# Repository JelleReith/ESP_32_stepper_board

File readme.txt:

Hi,
Thanks for using this board!

Hardware:
1 x ESP32 Devkit v1
9 x DRV8825 stepper driver
9 x 100uf 50v capacitor
pin_headers or screw terminals.

      //////////////////////BOARD LAYOUT\\\\\\\\\\\\\\\\\\\\\\\
      
 DIPDIP VESPVMOT  DRV0  DRV1  DRV2  DRV3  DRV4  DRV5  DRV6  DRV7  DRV8
 DIPDIP
ESPESPESPESPESP    CAP     DRV0DRV0DRV0  DRV5DRV5DRV5 CAP DRV6DRV6DRV6
ESPESPESPESPESP            DRV0DRV0DRV0  DRV5DRV5DRV5     DRV6DRV6DRV6
ESPESPESPESPESP            DRV0DRV0DRV0  DRV5DRV5DRV5 CAP DRV6DRV6DRV6
ESPESPESPESPESP
ESPESPESPESPESP    CAP     DRV1DRV1DRV1  DRV4DRV4DRV4 CAP DRV7DRV7DRV7
ESPESPESPESPESP            DRV1DRV1DRV1  DRV4DRV4DRV4     DRV7DRV7DRV7
ESPESPESPESPESP            DRV1DRV1DRV1  DRV4DRV4DRV4 CAP DRV7DRV7DRV7
ESPESPESPESPESP
ESPESPESPESPESP    CAP     DRV3DRV2DRV2  DRV3DRV3DRV3 CAP DRV8DRV8DRV8
ESPESPESPESPESP            DRV3DRV2DRV2  DRV3DRV3DRV3 CAP DRV8DRV8DRV8
ESPESPESPESPESP            DRV3DRV2DRV2  DRV3DRV3DRV3 CAP DRV8DRV8DRV8

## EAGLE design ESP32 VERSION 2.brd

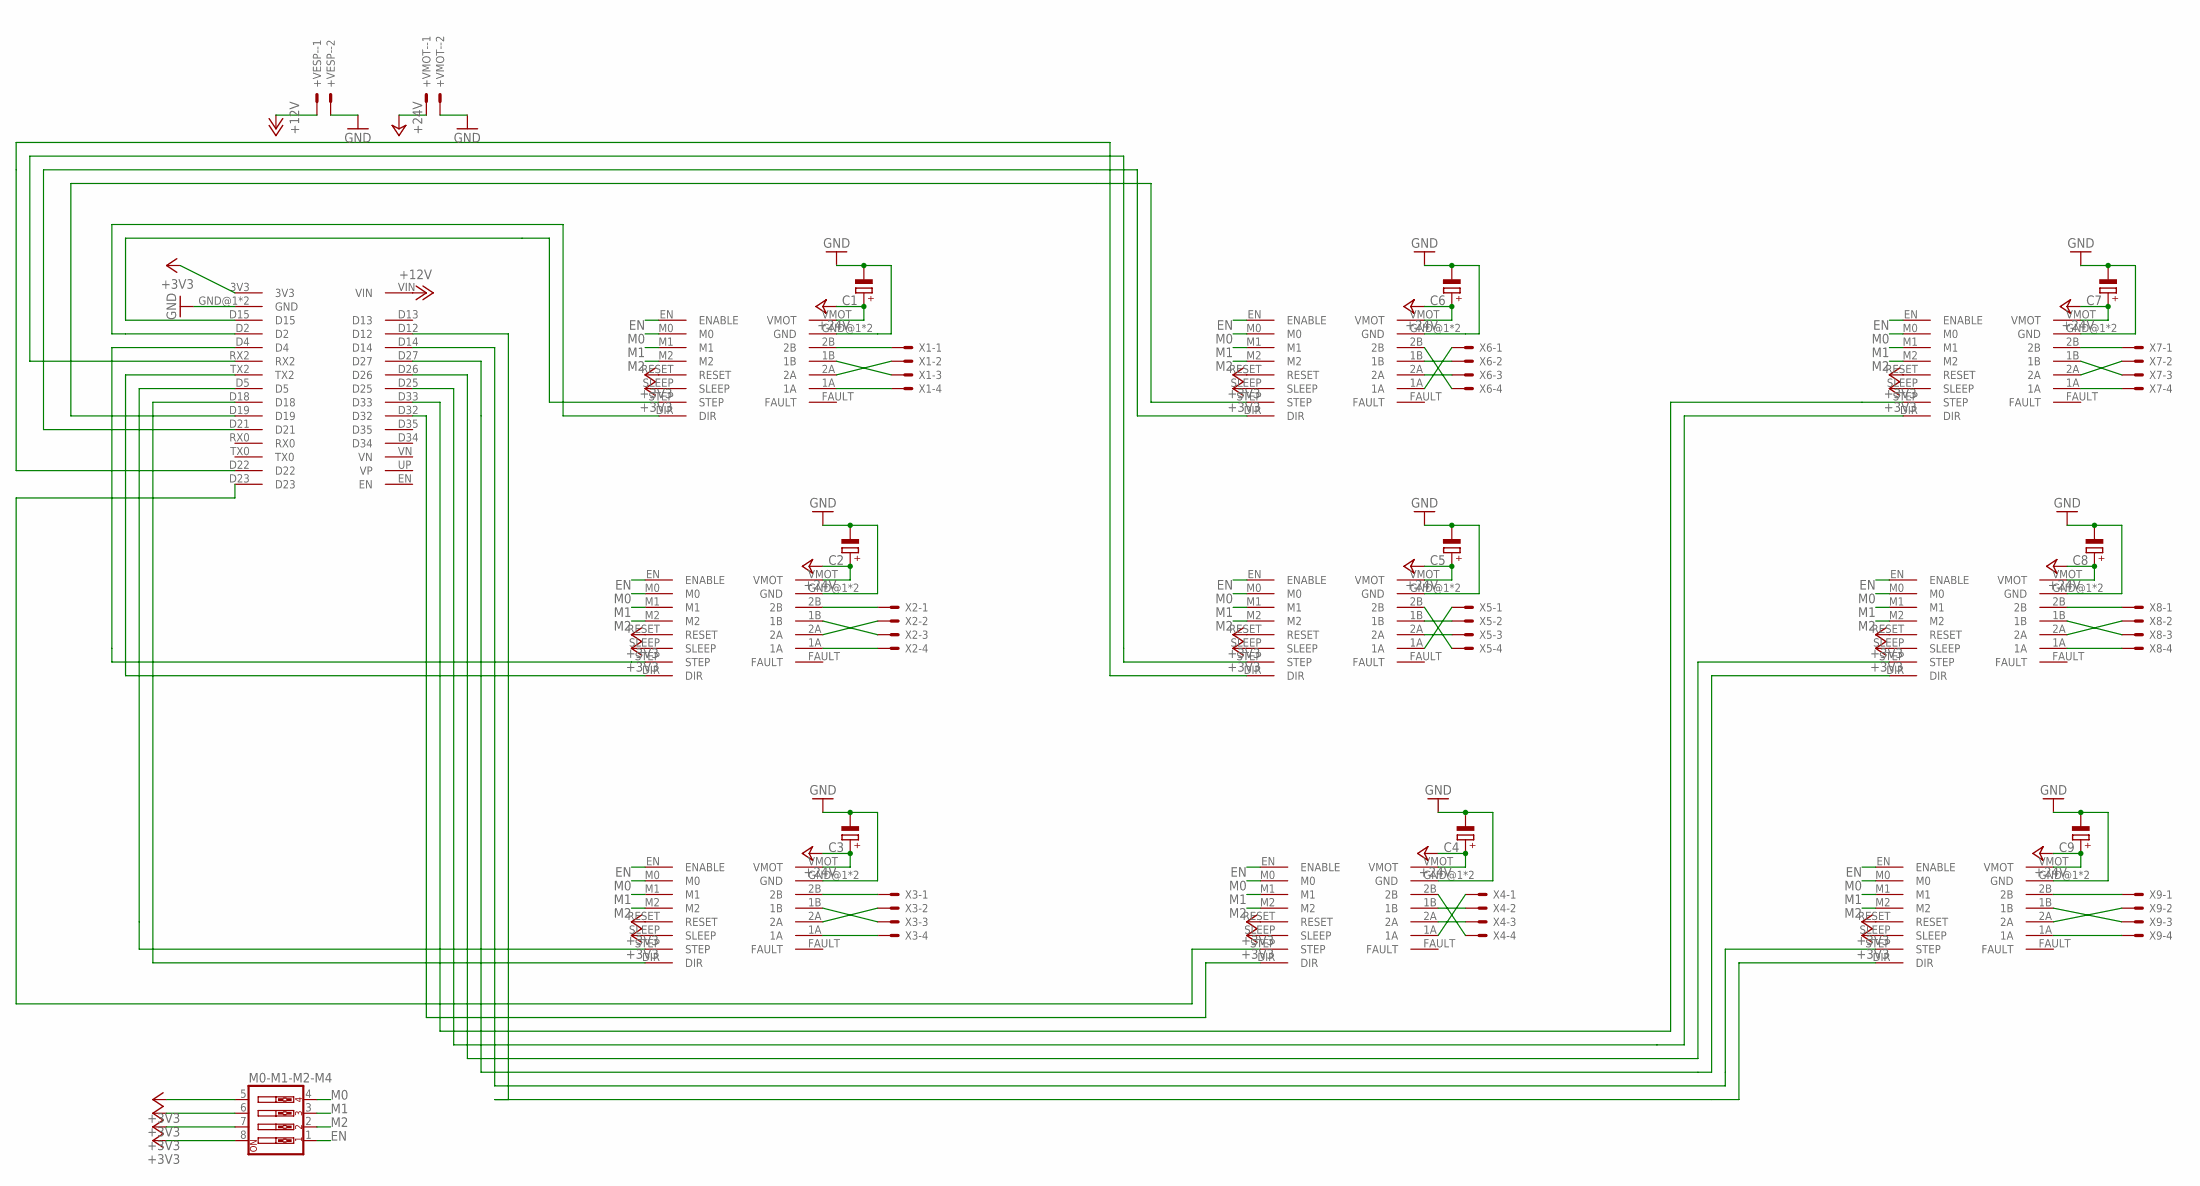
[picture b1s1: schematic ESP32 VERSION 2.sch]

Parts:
+VESP-: 22-23-2021
+VMOT-: 22-23-2021
C1, C2, C3, C4, C5, C6, C7, C8, C9: CPOL-EUE3.5-8; E3,5-8
M0-M1-M2-M4: SW_DIP-4; EDG-04
U$1, U$2, U$4, U$5, U$6, U$7, U$8, U$9: DRV8825
U$3: STEPPER 0; DRV8825
U$10: ESP32
X1, X2, X3, X4, X5, X6, X7, X8, X9: 22-23-2041

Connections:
+3V3: M0-M1-M2-M4.5, M0-M1-M2-M4.6, M0-M1-M2-M4.7, M0-M1-M2-M4.8, U$1.RESET, U$1.SLEEP, U$2.RESET, U$2.SLEEP, U$3.RESET, U$3.SLEEP, U$4.RESET, U$4.SLEEP, U$5.RESET, U$5.SLEEP, U$6.RESET, U$6.SLEEP, U$7.RESET, U$7.SLEEP, U$8.RESET, U$8.SLEEP, U$9.RESET, U$9.SLEEP, U$10.3V3
+12V: +VESP-.1, U$10.VIN
+24V: +VMOT-.1, C1.+, C2.+, C3.+, C4.+, C5.+, C6.+, C7.+, C8.+, C9.+, U$1.VMOT, U$2.VMOT, U$3.VMOT, U$4.VMOT, U$5.VMOT, U$6.VMOT, U$7.VMOT, U$8.VMOT, U$9.VMOT
EN: M0-M1-M2-M4.1, U$1.EN (ENABLE), U$2.EN (ENABLE), U$3.EN (ENABLE), U$4.EN (ENABLE), U$5.EN (ENABLE), U$6.EN (ENABLE), U$7.EN (ENABLE), U$8.EN (ENABLE), U$9.EN (ENABLE)
GND: +VESP-.2, +VMOT-.2, C1.-, C2.-, C3.-, C4.-, C5.-, C6.-, C7.-, C8.-, C9.-, U$1.GND@1 (GND), U$1.GND@2 (GND), U$2.GND@1 (GND), U$2.GND@2 (GND), U$3.GND@1 (GND), U$3.GND@2 (GND), U$4.GND@1 (GND), U$4.GND@2 (GND), U$5.GND@1 (GND), U$5.GND@2 (GND), U$6.GND@1 (GND), U$6.GND@2 (GND), U$7.GND@1 (GND), U$7.GND@2 (GND), U$8.GND@1 (GND), U$8.GND@2 (GND), U$9.GND@1 (GND), U$9.GND@2 (GND), U$10.GND@1 (GND), U$10.GND@2 (GND)
M0: M0-M1-M2-M4.4, U$1.M0, U$2.M0, U$3.M0, U$4.M0, U$5.M0, U$6.M0, U$7.M0, U$8.M0, U$9.M0
M1: M0-M1-M2-M4.3, U$1.M1, U$2.M1, U$3.M1, U$4.M1, U$5.M1, U$6.M1, U$7.M1, U$8.M1, U$9.M1
M2: M0-M1-M2-M4.2, U$1.M2, U$2.M2, U$3.M2, U$4.M2, U$5.M2, U$6.M2, U$7.M2, U$8.M2, U$9.M2
unnamed: U$3.2B, X1.1
unnamed: U$9.1B, X9.3
unnamed: U$9.2A, X9.2
unnamed: U$3.1A, X1.4
unnamed: U$3.STEP, U$10.D15
unnamed: U$3.DIR, U$10.D2
unnamed: U$4.1A, X6.1
unnamed: U$4.2A, X6.3
unnamed: U$4.1B, X6.2
unnamed: U$4.2B, X6.4
unnamed: U$2.STEP, U$10.D4
unnamed: U$2.DIR, U$10.TX2
unnamed: U$7.2B, X7.1
unnamed: U$7.2A, X7.2
unnamed: U$7.1B, X7.3
unnamed: U$7.1A, X7.4
unnamed: U$1.STEP, U$10.D5
unnamed: U$2.2B, X2.1
unnamed: U$8.2B, X8.1
unnamed: U$8.1B, X8.3
unnamed: U$8.2A, X8.2
unnamed: U$8.1A, X8.4
unnamed: U$1.DIR, U$10.D18
unnamed: U$2.1B, X2.3
unnamed: U$9.2B, X9.1
unnamed: U$5.1B, X5.2
unnamed: U$5.2A, X5.3
unnamed: U$9.1A, X9.4
unnamed: U$4.DIR, U$10.D21
unnamed: U$2.2A, X2.2
unnamed: U$5.1A, X5.1
unnamed: U$5.2B, X5.4
unnamed: U$6.1B, X4.2
unnamed: U$6.2A, X4.3
unnamed: U$4.STEP, U$10.D19
unnamed: U$5.STEP, U$10.RX2
unnamed: U$6.2B, X4.4
unnamed: U$6.1A, X4.1
unnamed: U$1.1B, X3.3
unnamed: U$1.2A, X3.2
unnamed: U$5.DIR, U$10.D22
unnamed: U$2.1A, X2.4
unnamed: U$1.2B, X3.1
unnamed: U$3.1B, X1.3
unnamed: U$3.2A, X1.2
unnamed: U$1.1A, X3.4
unnamed: U$6.STEP, U$10.D23
unnamed: U$6.DIR, U$10.D32
unnamed: U$7.STEP, U$10.D33
unnamed: U$7.DIR, U$10.D25
unnamed: U$8.STEP, U$10.D26
unnamed: U$8.DIR, U$10.D27
unnamed: U$9.STEP, U$10.D14
unnamed: U$9.DIR, U$10.D12

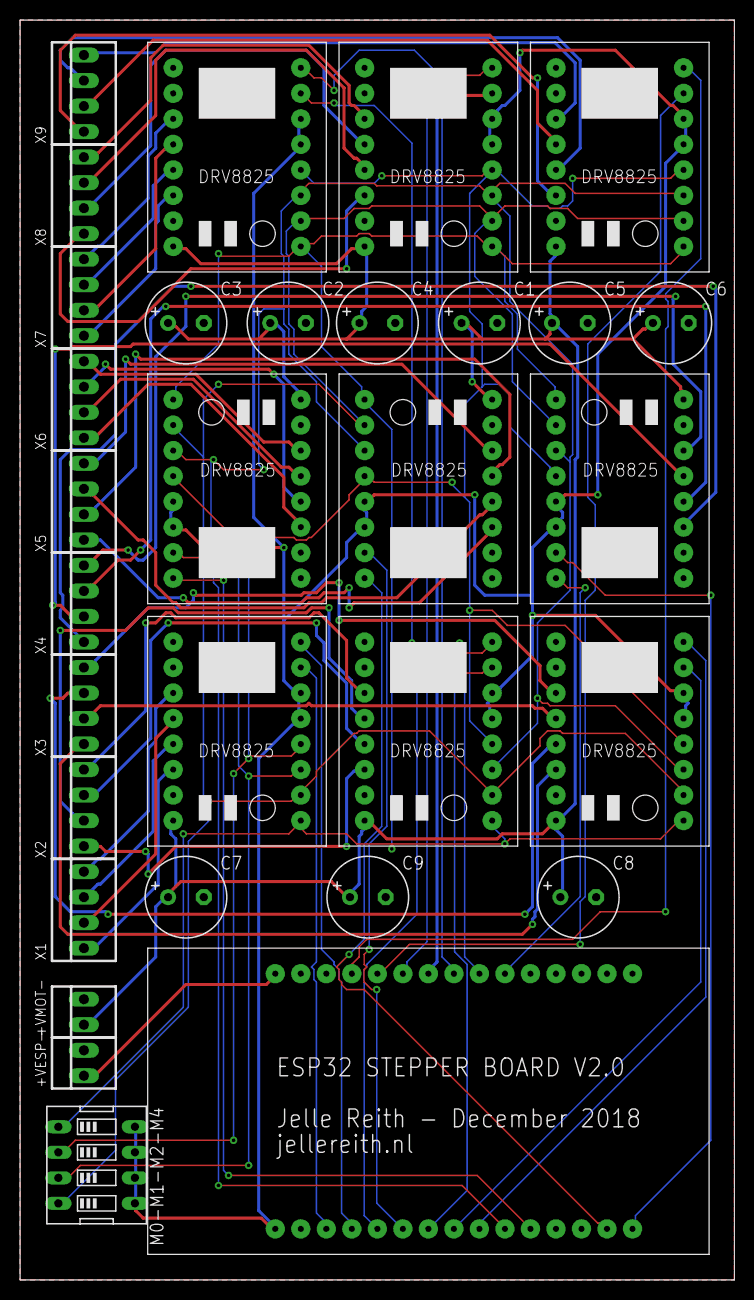
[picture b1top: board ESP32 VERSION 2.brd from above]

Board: 2 copper layers, 71.1 x 125.4 mm, 31 parts (0 on the bottom side), 62 nets.

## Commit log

2018-12-06 Add files via upload
    Software for EPS and processing sketch
    Libraries arduino:
    Accelstepper: https://www.airspayce.com/mikem/arduino/AccelStepper/
    OSC: https://github.com/CNMAT/OSC
2018-12-06 Add files via upload
    EAGLE files
